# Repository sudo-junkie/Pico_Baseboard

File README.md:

# Pico Baseboard

KiCad 7 design files (schematic, PCB, BOM, gerbers) for a Raspberry Pi Pico carrier board with 4 analog inputs and 4 digital I/O

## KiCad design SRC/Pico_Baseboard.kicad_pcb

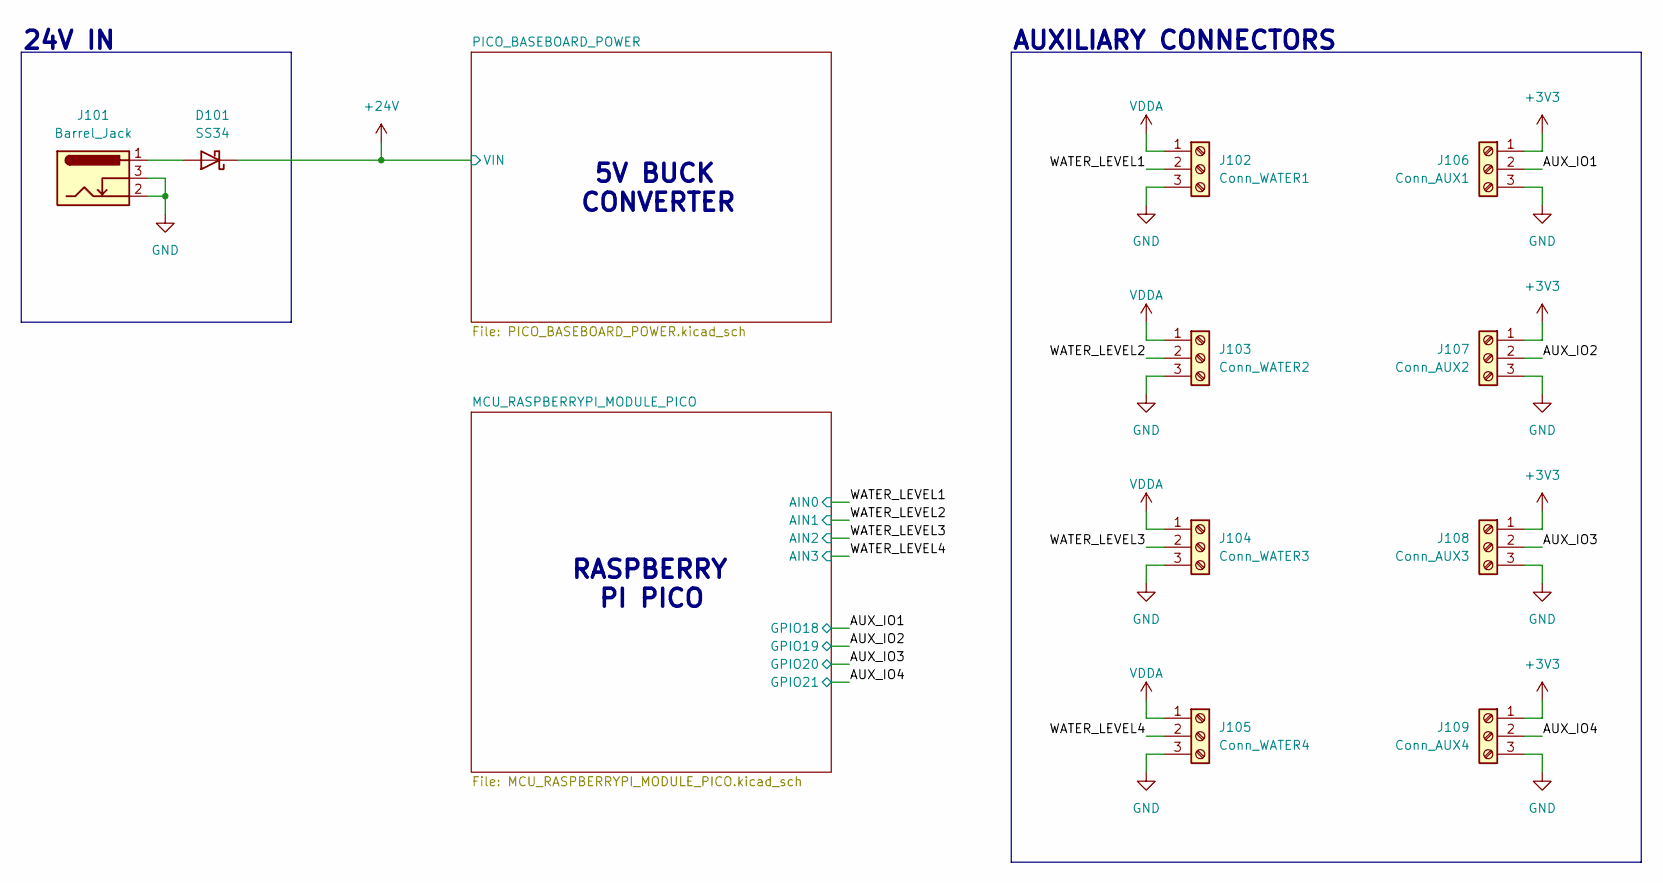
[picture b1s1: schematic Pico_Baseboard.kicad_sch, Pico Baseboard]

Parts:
D101: SS34; D_SOD-323; MPN 3DSR1M; JLCPCB PART# C5365547
J101: Barrel_Jack; BarrelJack_Horizontal; MPN HC-DC-005-2.0T; JLCPCB PART# C3010533
J102: Conn_WATER1; TerminalBlock_Phoenix_MPT-0,5-3-2.54_1x03_P2.54mm_Horizontal; MPN C68305; JLCPCB PART# C68305
J103: Conn_WATER2; TerminalBlock_Phoenix_MPT-0,5-3-2.54_1x03_P2.54mm_Horizontal; MPN C68305; JLCPCB PART# C68305
J104: Conn_WATER3; TerminalBlock_Phoenix_MPT-0,5-3-2.54_1x03_P2.54mm_Horizontal; MPN C68305; JLCPCB PART# C68305
J105: Conn_WATER4; TerminalBlock_Phoenix_MPT-0,5-3-2.54_1x03_P2.54mm_Horizontal; MPN C68305; JLCPCB PART# C68305
J106: Conn_AUX1; TerminalBlock_Phoenix_MPT-0,5-3-2.54_1x03_P2.54mm_Horizontal; MPN C68305; JLCPCB PART# C68305
J107: Conn_AUX2; TerminalBlock_Phoenix_MPT-0,5-3-2.54_1x03_P2.54mm_Horizontal; MPN C68305; JLCPCB PART# C68305
J108: Conn_AUX3; TerminalBlock_Phoenix_MPT-0,5-3-2.54_1x03_P2.54mm_Horizontal; MPN C68305; JLCPCB PART# C68305
J109: Conn_AUX4; TerminalBlock_Phoenix_MPT-0,5-3-2.54_1x03_P2.54mm_Horizontal; MPN C68305; JLCPCB PART# C68305

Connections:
+3V3: J106.1, J107.1, J108.1, J109.1; also elsewhere on the board
+24V: D101.1 (K); also elsewhere on the board
/AUX_IO1: J106.2; also elsewhere on the board
/AUX_IO2: J107.2; also elsewhere on the board
/AUX_IO3: J108.2; also elsewhere on the board
/AUX_IO4: J109.2; also elsewhere on the board
/WATER_LEVEL1: J102.2; also elsewhere on the board
/WATER_LEVEL2: J103.2; also elsewhere on the board
/WATER_LEVEL3: J104.2; also elsewhere on the board
/WATER_LEVEL4: J105.2; also elsewhere on the board
GND: J101.2, J101.3, J102.3, J103.3, J104.3, J105.3, J106.3, J107.3, J108.3, J109.3; also elsewhere on the board
unnamed: D101.2 (A), J101.1
VDDA: J102.1, J103.1, J104.1, J105.1; also elsewhere on the board

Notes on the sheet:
AUXILIARY CONNECTORS
24V IN
RASPBERRY PI PICO
5V BUCK CONVERTER

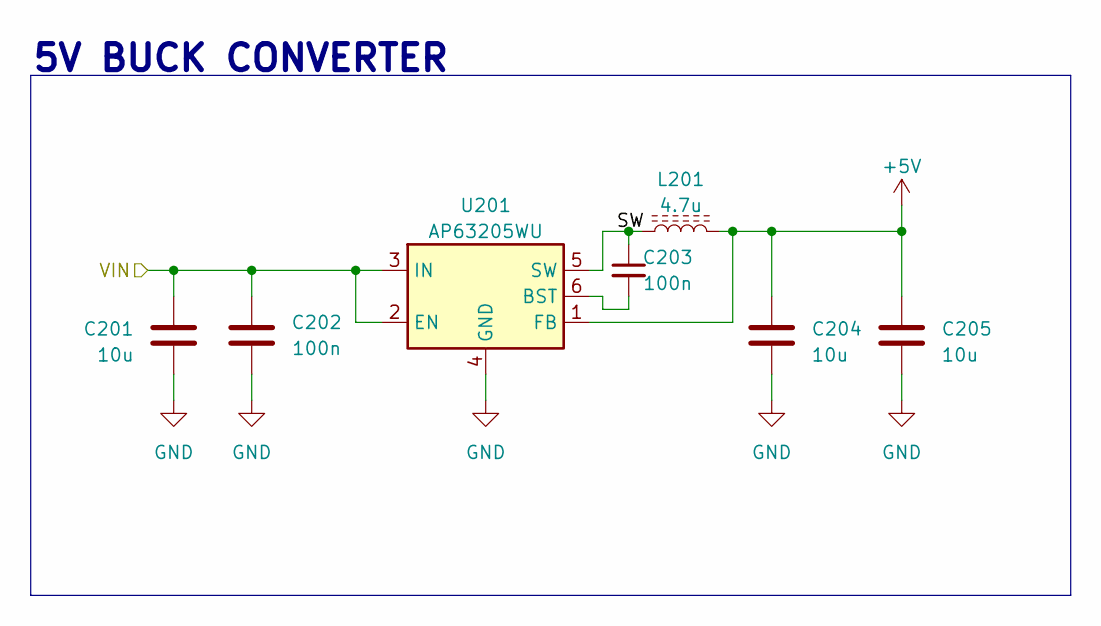
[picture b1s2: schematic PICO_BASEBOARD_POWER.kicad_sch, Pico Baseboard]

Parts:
C201, C204, C205: 10u; C_0402_1005Metric; MPN GRM188R61E106KA73D; JLCPCB PART# C344022
C202, C203: 100n; C_0402_1005Metric; MPN CL03A104KO3NNNC; JLCPCB PART# C307380
L201: 4.7u; L_Sunlord_MWSA0402S; MPN CXP0420-4R7M-AG(4.7uh); JLCPCB PART# C7187307
U201: AP63205WU; TSOT-23-6; MPN AP63205WU-7; JLCPCB PART# C2071056

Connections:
+5V: C204.1, C205.1, L201.2, U201.1 (FB); also elsewhere on the board
+24V: C201.1, C202.1, U201.2 (EN), U201.3 (IN); also elsewhere on the board
/PICO_BASEBOARD_POWER/SW: C203.1, L201.1, U201.5 (SW)
GND: C201.2, C202.2, C204.2, C205.2, U201.4 (GND); also elsewhere on the board
unnamed: C203.2, U201.6 (BST)

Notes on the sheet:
5V BUCK CONVERTER

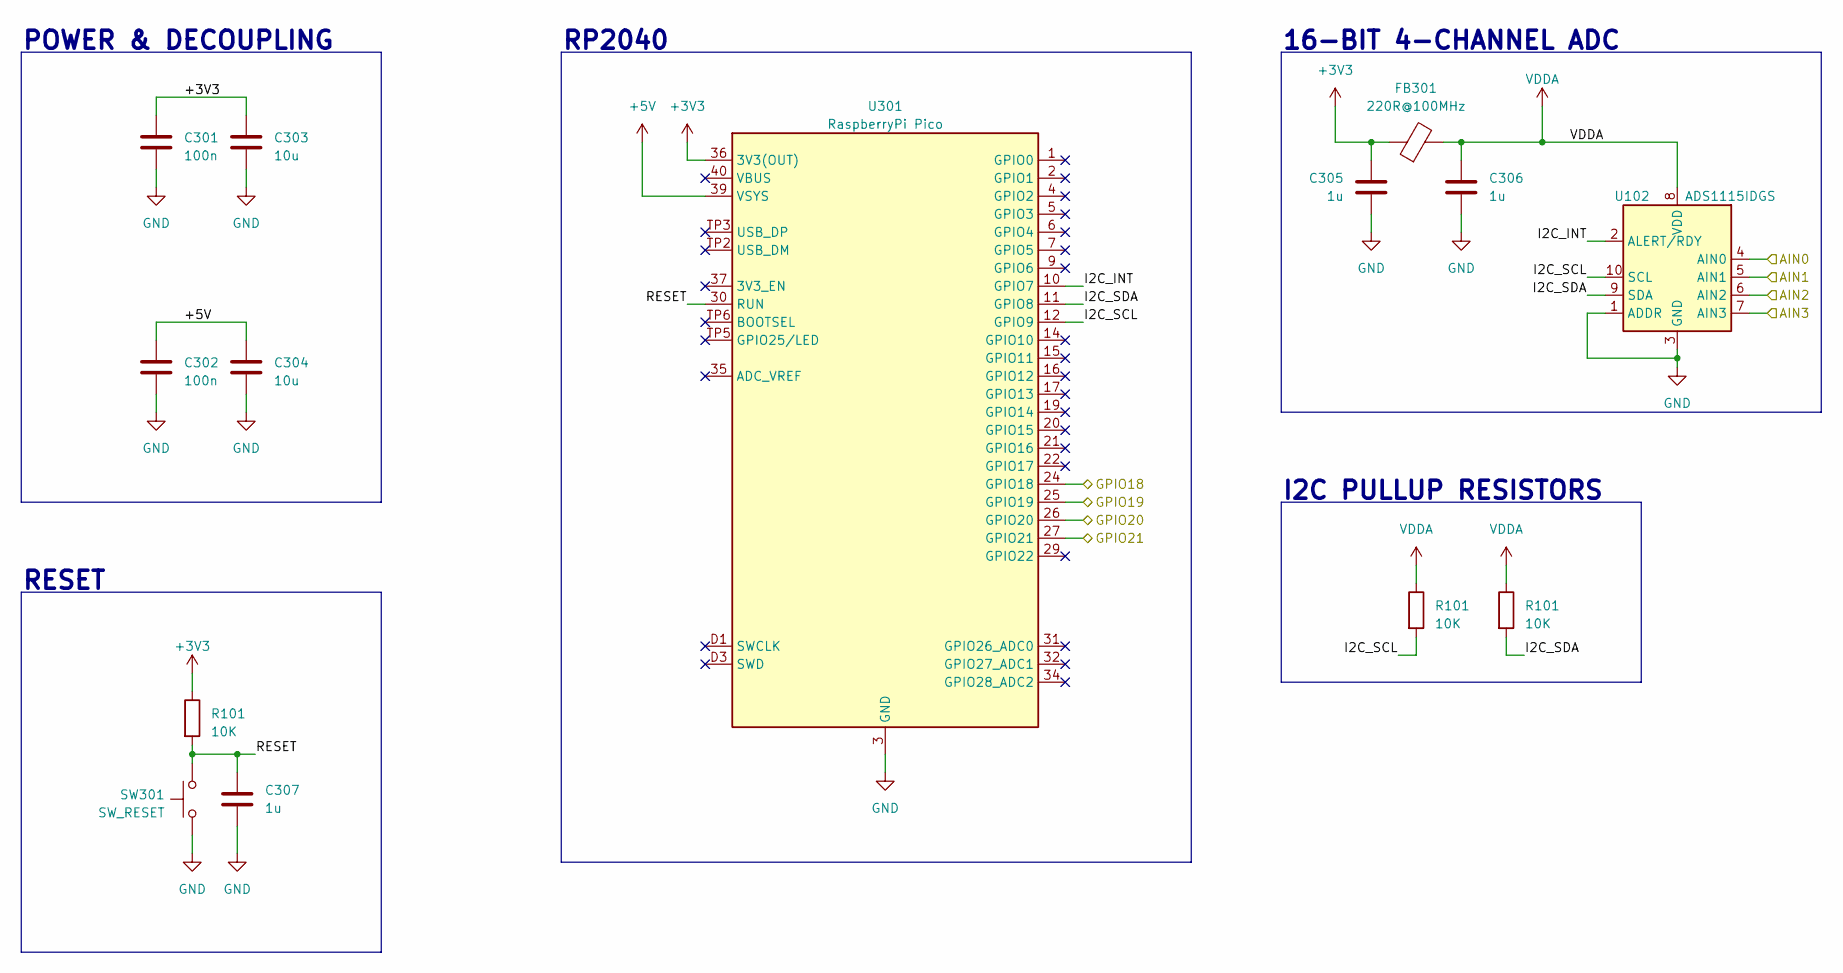
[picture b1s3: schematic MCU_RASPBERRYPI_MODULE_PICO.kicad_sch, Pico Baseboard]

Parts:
C301, C302: 100n; C_0402_1005Metric; MPN CL03A104KO3NNNC; JLCPCB PART# C307380
C303, C304: 10u; C_0402_1005Metric; MPN GRM188R61E106KA73D; JLCPCB PART# C344022
C305, C306, C307: 1u; C_0402_1005Metric; MPN CL05A105KO5NNNC; JLCPCB PART# C29266
FB301: 220R@100MHz; L_0402_1005Metric; MPN BLM15PG100SN1D; JLCPCB PART# C85823
R101: 10K; R_0402_1005Metric; MPN RC0402FR-0710KL; JLCPCB PART# C60490
SW301: SW_RESET; SW_SPST_B3U-1000P; MPN TD-1183SN-1.5H-250; JLCPCB PART# C2905193
U102: ADS1115IDGS; TSSOP-10_3x3mm_P0.5mm; MPN ADS1115IDGSR; JLCPCB PART# C37593
U301: RaspberryPi Pico; MPN PICO; JLCPCB PART# C7203002

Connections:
+3V3: C301.1, C303.1, C305.1, FB301.1, U301.36 (3V3(OUT)); also elsewhere on the board
+5V: C302.1, C304.1, U301.39 (VSYS); also elsewhere on the board
/AUX_IO1: U301.24 (GPIO18); also elsewhere on the board
/AUX_IO2: U301.25 (GPIO19); also elsewhere on the board
/AUX_IO3: U301.26 (GPIO20); also elsewhere on the board
/AUX_IO4: U301.27 (GPIO21); also elsewhere on the board
/MCU_RASPBERRYPI_MODULE_PICO/I2C_INT: U301.10 (GPIO7); also elsewhere on the board
/MCU_RASPBERRYPI_MODULE_PICO/I2C_SCL: U301.12 (GPIO9); also elsewhere on the board
/MCU_RASPBERRYPI_MODULE_PICO/I2C_SDA: U301.11 (GPIO8); also elsewhere on the board
/MCU_RASPBERRYPI_MODULE_PICO/RESET: C307.1, SW301.2, U301.30 (RUN); also elsewhere on the board
GND: C301.2, C302.2, C303.2, C304.2, C305.2, C306.2, C307.2, SW301.1, U301.3 (GND), U301.8 (GND), U301.13 (GND), U301.18 (GND), U301.23 (GND), U301.28 (GND), U301.33 (GND), U301.38 (GND), U301.A (GND), U301.B (GND), U301.C (GND), U301.D (GND), U301.D2 (GND), U301.TP1 (GND); also elsewhere on the board
VDDA: C306.1, FB301.2; also elsewhere on the board

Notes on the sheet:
POWER & DECOUPLING
I2C PULLUP RESISTORS
RP2040
RESET
16-BIT 4-CHANNEL ADC

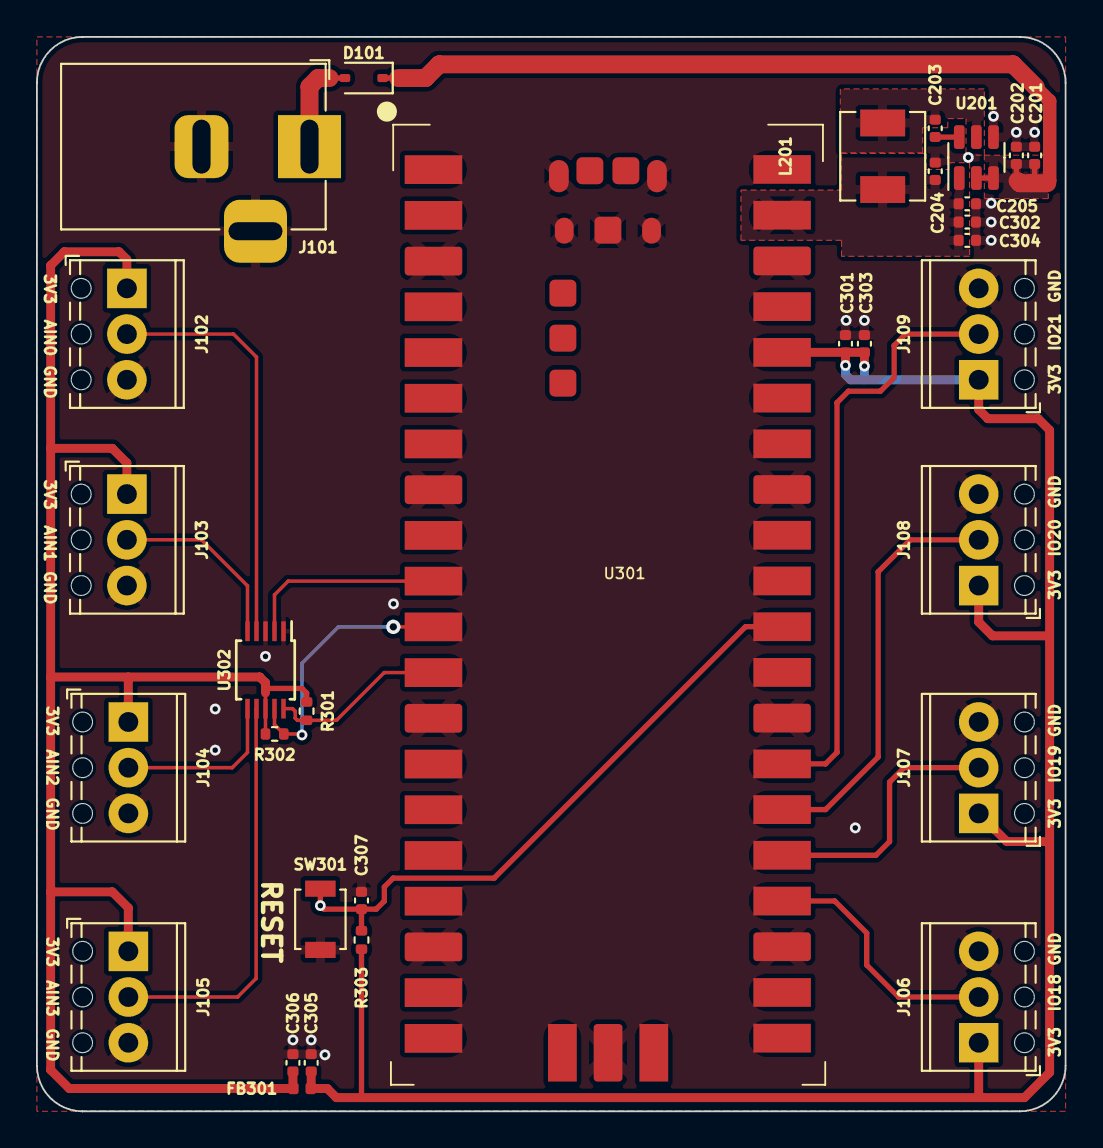
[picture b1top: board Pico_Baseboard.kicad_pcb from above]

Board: 2 copper layers, 57.2 x 59.7 mm, 31 parts (0 on the bottom side), 20 nets.

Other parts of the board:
R301, R302, R303: 10K; R_0402_1005Metric
U302: ADS1115IDGS; TSSOP-10_3x3mm_P0.5mm

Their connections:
+3V3: R303.1; also elsewhere on the board
/MCU_RASPBERRYPI_MODULE_PICO/I2C_INT: U302.2 (ALERT/RDY); also elsewhere on the board
/MCU_RASPBERRYPI_MODULE_PICO/I2C_SCL: R301.2, U302.10 (SCL); also elsewhere on the board
/MCU_RASPBERRYPI_MODULE_PICO/I2C_SDA: R302.2, U302.9 (SDA); also elsewhere on the board
/MCU_RASPBERRYPI_MODULE_PICO/RESET: R303.2; also elsewhere on the board
/WATER_LEVEL1: U302.4 (AIN0); also elsewhere on the board
/WATER_LEVEL2: U302.5 (AIN1); also elsewhere on the board
/WATER_LEVEL3: U302.6 (AIN2); also elsewhere on the board
/WATER_LEVEL4: U302.7 (AIN3); also elsewhere on the board
GND: U302.1 (ADDR), U302.3 (GND); also elsewhere on the board
VDDA: R301.1, R302.1, U302.8 (VDD); also elsewhere on the board
